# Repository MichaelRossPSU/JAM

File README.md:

# JAM
EE 403W Repository - John Darling, Alex Swan Yi, Michael Ross

John Darling (darling.johnt@gmail.com)
Thadoe Swan Yi (tis5323@psu.edu)
Michael Ross (mur5009@psu.edu)

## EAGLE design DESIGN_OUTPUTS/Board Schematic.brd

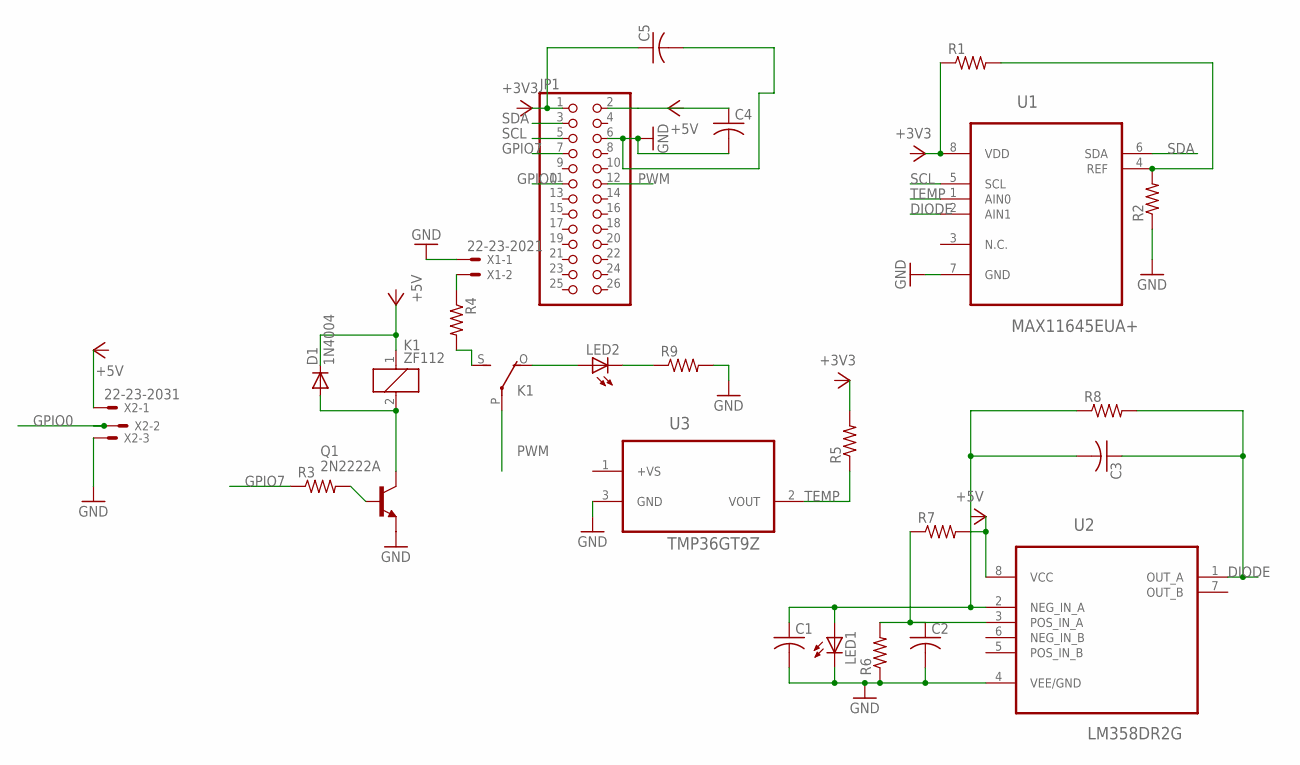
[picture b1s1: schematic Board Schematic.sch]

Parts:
C1, C2, C3, C4, C5: C-USC1206; C1206
D1: 1N4004; DO41-10
JP1: PINHD-2X13; 2X13
K1: ZF112
LED1, LED2: LED5MM
Q1: 2N2222A; TO18
R1, R2, R3, R4, R5, R6, R7, R8, R9: R-US_R1206; R1206
U1: MAX11645EUA+; SOP65P490X110-8N
U2: LM358DR2G; SOIC127P600X175-8N
U3: TMP36GT9Z; TO127P254X533-3P
X1: 22-23-2021
X2: 22-23-2031

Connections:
3V3: C5.1, JP1.1, R1.1, R5.2, U1.8 (VDD)
+5V: C4.1, D1.C, JP1.2, K1.1, R7.2, U2.8 (VCC), X2.1
+VS: U3.1 (+VS)
DIODE: C3.1, R8.2, U1.2 (AIN1), U2.1 (OUT_A)
GND: C1.2, C2.2, C4.2, C5.2, JP1.6, LED1.K (C), Q1.1 (E), R2.1, R6.1, R9.2, U1.7 (GND), U2.4 (VEE/GND), U3.3 (GND), X1.1, X2.3
GPIO0: JP1.11, X2.2
GPIO7: JP1.7, R3.1
unnamed: R1.2, R2.2, U1.4 (REF)
unnamed: R4.1, X1.2
unnamed: C1.1, C3.2, LED1.A, R8.1, U2.2 (NEG_IN_A)
unnamed: C2.1, R6.2, R7.1, U2.3 (POS_IN_A)
unnamed: K1.O, LED2.A
unnamed: D1.A, K1.2, Q1.3 (C)
unnamed: Q1.2 (B), R3.2
unnamed: K1.S, R4.2
unnamed: LED2.K (C), R9.1
PWM: JP1.12, K1.P
SCL: JP1.5, U1.5 (SCL)
SDA: JP1.3, U1.6 (SDA)
TEMP: R5.1, U1.1 (AIN0), U3.2 (VOUT)

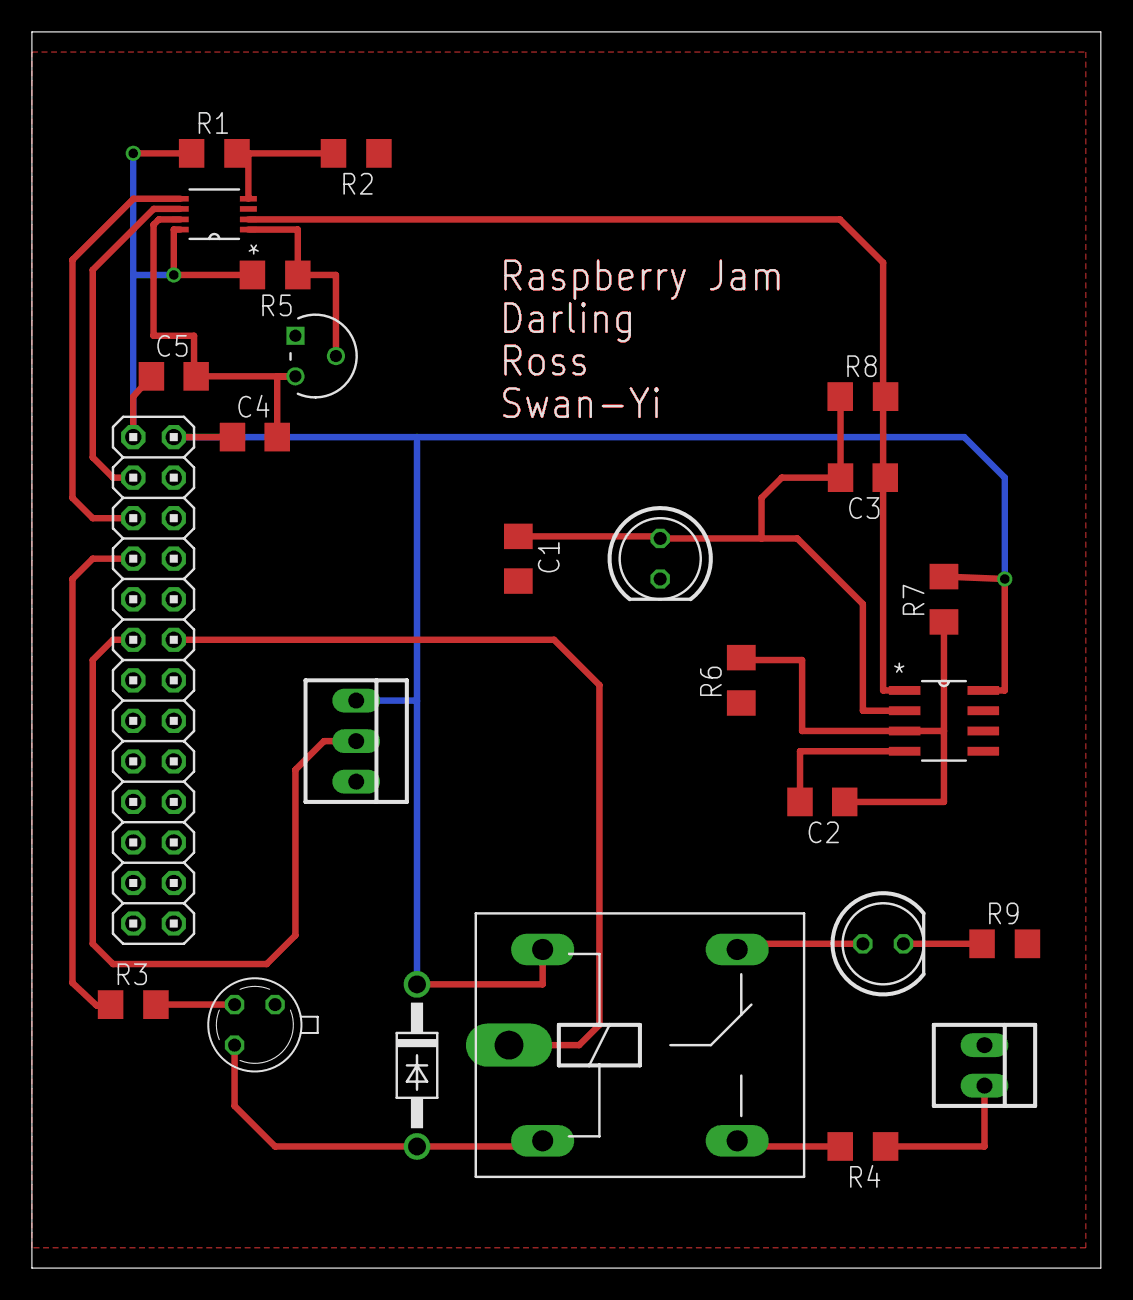
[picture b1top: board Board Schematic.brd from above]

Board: 2 copper layers, 67.0 x 77.5 mm, 25 parts (0 on the bottom side), 19 nets.

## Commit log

2016-01-22 Project Statement
2016-01-25 Adding a test.txt
2016-01-25 Added test python
2016-02-01 Added Design Proposal
2016-02-02 Deleted a test file
2016-02-02 Deleted test files
2016-02-15 Added index.html in CURRENT_VERSIONS folder
2016-02-15 Added web socket python code
2016-03-02 Added Design Review ppt
2016-03-14 Added Eagle Board File
2016-03-14 Created Software Folder
2016-03-16 Design Review Grades
2016-04-19 Added new index.html and IR sensor code.
2016-04-25 added project demo file
2016-05-02 Added Final Report
2017-07-05 css for index.html
